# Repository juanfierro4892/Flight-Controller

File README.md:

Flight Controller 

This is a custom flight controller designed for control rockets.
It uses an STM32F722 microcontroller, ICM-45686 IMU, BMP580 barometer, and has a microSD card for logging flight data. It supports 2S LiPo batteries with onboard charging and has PWM outputs for controlling servos.

The board was designed in KiCad and is fully open source.

PCB: 

3D image: 

Schematic: 

Assembly:

There is no assembly instructions because as it have a lot of components there come assembled from the manufacturer aka JLCPCB

Technical Specifications
Brain: STM32F722RET6 microcontroller.

IMU: ICM-45686 high-precision motion sensor.

Barometer: BMP580 altitude tracker.

Actuation: Multi-channel Servo output via PWM.

Data Logging: Onboard MicroSD card slot.

Power Management:

BQ25883: 2-cell LiPo battery charger via USB-C.

TPS63070: 5V Buck-Boost regulator for servos.

LMR51430: 3.3V Buck regulator for the MCU and sensors..

D2: RGB LED (Common Anode) — Visual status indicator for system boot, ready-to-fly state, and critical errors (IMU, battery, SD card, and power rails).

It is coded in C in visual studio code.

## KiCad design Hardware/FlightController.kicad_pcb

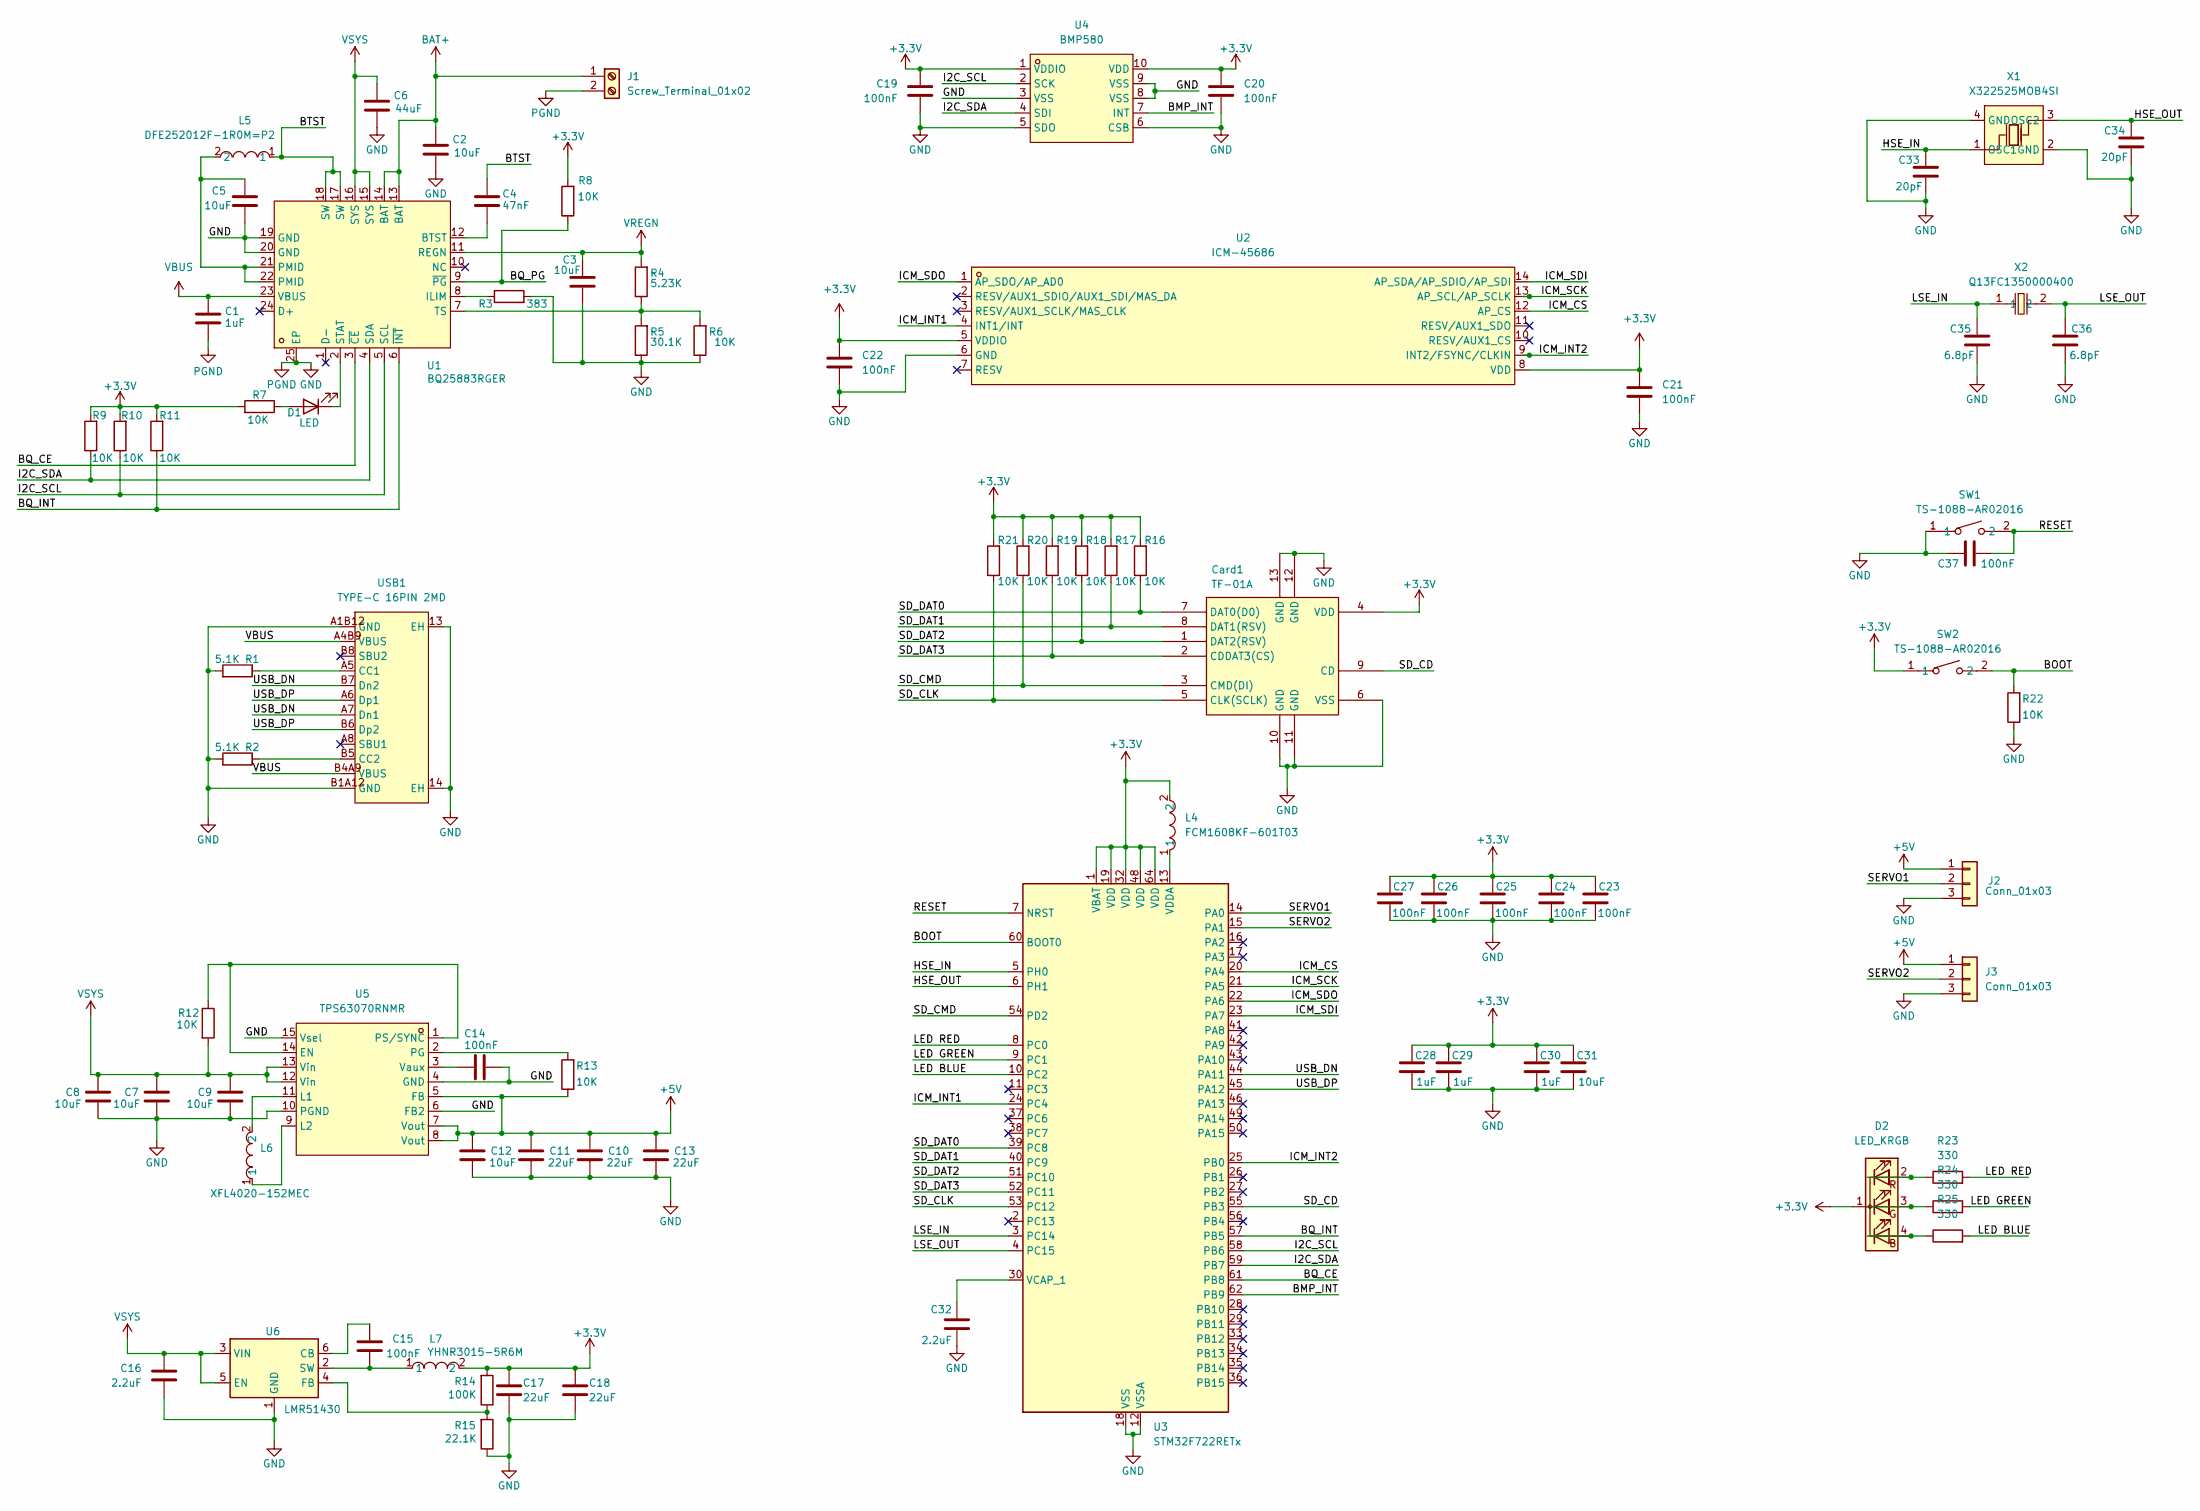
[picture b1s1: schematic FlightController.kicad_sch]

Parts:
C1, C28, C29, C30: 1uF; C_0402_1005Metric
C2, C9, C12: 10uF; C_0603_1608Metric
C3, C5, C31: 10uF; C_0402_1005Metric
C4: 47nF; C_0201_0603Metric
C6: 44uF; C_0603_1608Metric
C7, C8: 10uF; C_0805_2012Metric
C10, C11, C13: 22uF; C_0805_2012Metric
C14, C15, C19, C20, C21, C22, C23, C24, C25, C26, C27, C37: 100nF; C_0201_0603Metric
C16: 2.2uF; C_0603_1608Metric
C17, C18: 22uF; C_0402_1005Metric
C32: 2.2uF; C_0201_0603Metric
C33, C34: 20pF; C_0201_0603Metric
C35, C36: 6.8pF; C_0201_0603Metric
Card1: TF-01A; TF-SMD_TF-01A; LCSC Part C91145
D1: LED; LED_0402_1005Metric
D2: LED_KRGB; LED_Avago_PLCC4_3.2x2.8mm_CW
J1: Screw_Terminal_01x02; TerminalBlock_Xinya_XY308-2.54-2P_1x02_P2.54mm_Horizontal
J2, J3: Conn_01x03; PinHeader_1x03_P2.54mm_Vertical
L4: FCM1608KF-601T03; L0603; LCSC Part C141723
L5: DFE252012F-1R0M=P2; L2520; LCSC Part C435392
L6: XFL4020-152MEC; IND-SMD_L4.0-W4.0-A; LCSC Part C3033018
L7: YHNR3015-5R6M; IND-SMD_L3.0-W3.0; LCSC Part C18236327
R1, R2: 5.1K; R_0201_0603Metric
R3: 383; R_0201_0603Metric
R4: 5.23K; R_0201_0603Metric
R5: 30.1K; R_0201_0603Metric
R6, R7, R8, R9, R10, R11, R12, R13, R16, R17, R18, R19, R20, R21, R22: 10K; R_0201_0603Metric
R14: 100K; R_0402_1005Metric
R15: 22.1K; R_0402_1005Metric
R23, R24, R25: 330; R_0201_0603Metric
SW1, SW2: TS-1088-AR02016; SW-SMD_L3.9-W3.0-P4.45; LCSC Part C720477
U1: BQ25883RGER; VFQFPN-24_L4.0-W4.0-P0.50-BL-EP2.8; LCSC Part C544362
U2: ICM-45686; LGA-14_L3.0-W2.5-P0.50-TL; LCSC Part C22459454
U3: STM32F722RETx; LQFP-64_10x10mm_P0.5mm
U4: BMP580; LGA-10_L2.0-W2.0-P0.50-TL_BMP580; LCSC Part C22391138
U5: TPS63070RNMR; VQFN-HR-15_L3.0-W2.5-P0.50-BL_TPS63070RNMR; LCSC Part C109322
U6: LMR51430; SOT-23-6
USB1: TYPE-C 16PIN 2MD; USB-C-SMD_TYPE-C-16PIN-2MD-073; MPN TYPE-C 16PIN 2MD(073); LCSC Part C2765186
X1: X322525MOB4SI; CRYSTAL-SMD_4P-L3.2-W2.5-BL; LCSC Part C9006
X2: Q13FC1350000400; FC-135R_L3.2-W1.5; LCSC Part C32346

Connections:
+3.3V: C17.1, C18.1, C19.1, C20.1, C21.1, C22.1, C23.1, C24.1, C25.1, C26.1, C27.1, C28.1, C29.1, C30.1, C31.1, Card1.4 (VDD), D2.1 (K), L4.2, L7.2, R7.2, R8.2, R9.2, R10.2, R11.2, R14.2, R16.2, R17.2, R18.2, R19.2, R20.2, R21.2, SW2.1, U2.5 (VDDIO), U2.8 (VDD), U3.1 (VBAT), U3.19 (VDD), U3.32 (VDD), U3.48 (VDD), U3.64 (VDD), U4.1 (VDDIO), U4.10 (VDD)
+5V: C10.1, C11.1, C12.1, C13.1, J2.1, J3.1, R13.1, U5.5 (FB), U5.7 (Vout), U5.8 (Vout)
/BMP_INT: U3.62 (PB9), U4.7 (INT)
/BOOT: R22.2, SW2.2, U3.60 (BOOT0)
/BQ_CE: U1.3 (~CE), U3.61 (PB8)
/BQ_INT: R11.1, U1.6 (~INT), U3.57 (PB5)
/BQ_PG: R8.1, U1.9 (~PG)
/BTST: C4.1, L5.1, U1.17 (SW), U1.18 (SW)
/HSE_IN: C33.1, U3.5 (PH0), X1.1 (OSC1)
/HSE_OUT: C34.1, U3.6 (PH1), X1.3 (OSC2)
/I2C_SCL: R10.1, U1.5 (SCL), U3.58 (PB6), U4.2 (SCK)
/I2C_SDA: R9.1, U1.4 (SDA), U3.59 (PB7), U4.4 (SDI)
/ICM_CS: U2.12 (AP_CS), U3.20 (PA4)
/ICM_INT1: U2.4 (INT1/INT), U3.24 (PC4)
/ICM_INT2: U2.9 (INT2/FSYNC/CLKIN), U3.25 (PB0)
/ICM_SCK: U2.13 (AP_SCL/AP_SCLK), U3.21 (PA5)
/ICM_SDI: U2.14 (AP_SDA/AP_SDIO/AP_SDI), U3.23 (PA7)
/ICM_SDO: U2.1 (AP_SDO/AP_AD0), U3.22 (PA6)
/LED BLUE: R25.2, U3.10 (PC2)
/LED GREEN: R24.2, U3.9 (PC1)
/LED RED: R23.2, U3.8 (PC0)
/LSE_IN: C35.1, U3.3 (PC14), X2.1
/LSE_OUT: C36.1, U3.4 (PC15), X2.2
/RESET: C37.2, SW1.2, U3.7 (NRST)
/SD_CD: Card1.9 (CD), U3.55 (PB3)
/SD_CLK: Card1.5 (CLK(SCLK)), R21.1, U3.53 (PC12)
/SD_CMD: Card1.3 (CMD(DI)), R20.1, U3.54 (PD2)
/SD_DAT0: Card1.7 (DAT0(D0)), R16.1, U3.39 (PC8)
/SD_DAT1: Card1.8 (DAT1(RSV)), R17.1, U3.40 (PC9)
/SD_DAT2: Card1.1 (DAT2(RSV)), R18.1, U3.51 (PC10)
/SD_DAT3: Card1.2 (CDDAT3(CS)), R19.1, U3.52 (PC11)
/SERVO1: J2.2, U3.14 (PA0)
/SERVO2: J3.2, U3.15 (PA1)
/USB_DN: U3.44 (PA11), USB1.A7 (Dn1), USB1.B7 (Dn2)
/USB_DP: U3.45 (PA12), USB1.A6 (Dp1), USB1.B6 (Dp2)
BAT+: C2.1, J1.1, U1.13 (BAT), U1.14 (BAT)
GND: C1.2, C2.2, C3.2, C5.2, C6.2, C7.2, C8.2, C9.2, C10.2, C11.2, C12.2, C13.2, C14.2, C16.2, C17.2, C18.2, C19.2, C20.2, C21.2, C22.2, C23.2, C24.2, C25.2, C26.2, C27.2, C28.2, C29.2, C30.2, C31.2, C32.2, C33.2, C34.2, C35.2, C36.2, C37.1, Card1.6 (VSS), Card1.10 (GND), Card1.11 (GND), Card1.12 (GND), Card1.13 (GND), J1.2, J2.3, J3.3, R1.2, R2.2, R3.2, R5.1, R6.1, R15.1, R22.1, SW1.1, U1.19 (GND), U1.20 (GND), U1.25 (EP), U2.6 (GND), U3.12 (VSSA), U3.18 (VSS), U3.31 (VSS), U3.47 (VSS), U3.63 (VSS), U4.3 (VSS), U4.5 (SDO), U4.6 (CSB), U4.8 (VSS), U4.9 (VSS), U5.4 (GND), U5.6 (FB2), U5.10 (PGND), U5.15 (Vsel), U6.1 (GND), USB1.13 (EH), USB1.14 (EH), USB1.A1B12 (GND), USB1.B1A12 (GND), X1.2 (GND), X1.4 (GND)
unnamed: C5.1, L5.2, U1.21 (PMID), U1.22 (PMID)
unnamed: D1.2 (A), R7.1
unnamed: D1.1 (K), U1.2 (STAT)
unnamed: D2.4 (BA), R25.1
unnamed: D2.3 (GA), R24.1
unnamed: D2.2 (RA), R23.1
unnamed: C4.2, U1.12 (BTST)
unnamed: R3.1, U1.8 (ILIM)
unnamed: R4.1, R5.2, R6.2, U1.7 (TS)
unnamed: C32.1, U3.30 (VCAP_1)
unnamed: L4.1, U3.13 (VDDA)
unnamed: R12.1, U5.1 (PS/SYNC), U5.14 (EN)
unnamed: L6.2, U5.11 (L1)
unnamed: L6.1, U5.9 (L2)
unnamed: R13.2, U5.2 (PG)
unnamed: C14.1, U5.3 (Vaux)
unnamed: C15.1, U6.6 (CB)
unnamed: R14.1, R15.2, U6.4 (FB)
unnamed: C15.2, L7.1, U6.2 (SW)
unnamed: R1.1, USB1.A5 (CC1)
unnamed: R2.1, USB1.B5 (CC2)
VBUS: C1.1, U1.23 (VBUS), USB1.A4B9 (VBUS), USB1.B4A9 (VBUS)
VREGN: C3.1, R4.2, U1.11 (REGN)
VSYS: C6.1, C7.1, C8.1, C9.1, C16.1, R12.2, U1.15 (SYS), U1.16 (SYS), U5.12 (Vin), U5.13 (Vin), U6.3 (VIN), U6.5 (EN)

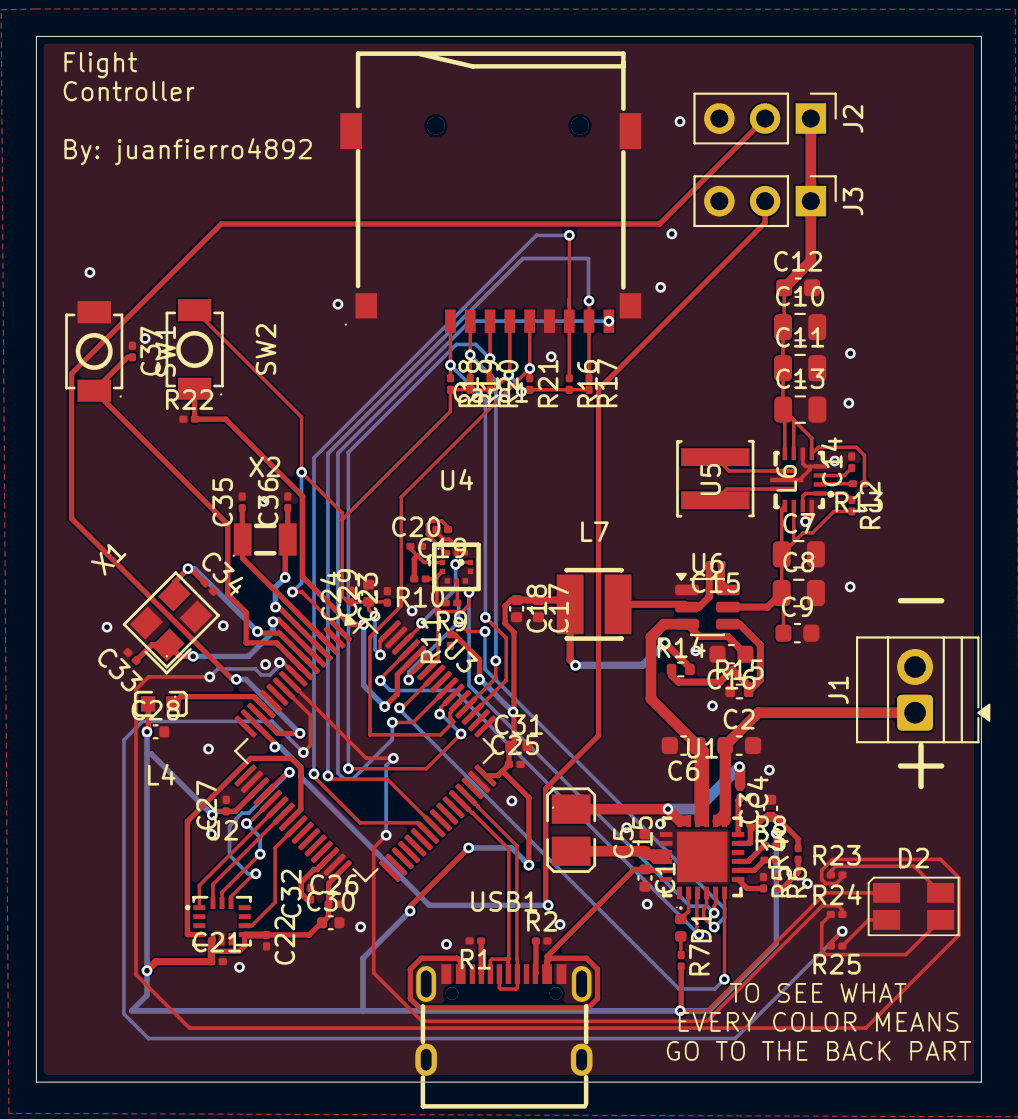
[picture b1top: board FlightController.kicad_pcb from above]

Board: 2 copper layers, 52.5 x 58.1 mm, 83 parts (0 on the bottom side), 61 nets.

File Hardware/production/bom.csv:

Designator,Footprint,Quantity,Value,LCSC Part #
"C1, C28, C29, C30",0402,4,1uF,
"C10, C11, C13",0805,3,22uF,
"C12, C2, C9",0603,3,10uF,
"C14, C15, C19, C20, C21, C22, C23, C24, C25, C26, C27, C37",0201,12,100nF,
C16,0603,1,2.2uF,
"C17, C18",0402,2,22uF,
"C3, C31, C5",0402,3,10uF,
C32,0201,1,2.2uF,
"C33, C34",0201,2,20pF,
"C35, C36",0201,2,6.8pF,
C4,0201,1,47nF,
C6,0603,1,44uF,
"C7, C8",0805,2,10uF,
CARD1,TF-SMD_TF-01A,1,TF-01A,C91145
D1,0402,1,LED,
D2,LED_Avago_PLCC4_3.2x2.8mm_CW,1,LED_KRGB,
J1,TerminalBlock_Xinya_XY308-2.54-2P_1x02_P2.54mm_Horizontal,1,Screw_Terminal_01x02,
"J2, J3",PinHeader_1x03_P2.54mm_Vertical,2,Conn_01x03,
L4,L0603,1,FCM1608KF-601T03,C141723
L5,L2520,1,DFE252012F-1R0M=P2,C435392
L6,IND-SMD_L4.0-W4.0-A,1,XFL4020-152MEC,C3033018
L7,IND-SMD_L3.0-W3.0,1,YHNR3015-5R6M,C18236327
"R1, R2",0201,2,5.1K,
"R10, R11, R12, R13, R16, R17, R18, R19, R20, R21, R22, R6, R7, R8, R9",0201,15,10K,
R14,0402,1,100K,
R15,0402,1,22.1K,
"R23, R24, R25",0201,3,330,
R3,0201,1,383,
R4,0201,1,5.23K,
R5,0201,1,30.1K,
"SW1, SW2",SW-SMD_L3.9-W3.0-P4.45,2,TS-1088-AR02016,C720477
U1,VFQFPN-24_L4.0-W4.0-P0.50-BL-EP2.8,1,BQ25883RGER,C544362
U2,LGA-14_L3.0-W2.5-P0.50-TL,1,ICM-45686,C22459454
U3,LQFP-64_10x10mm_P0.5mm,1,STM32F722RETx,
U4,LGA-10_L2.0-W2.0-P0.50-TL_BMP580,1,BMP580,C22391138
U5,VQFN-HR-15_L3.0-W2.5-P0.50-BL_TPS63070RNMR,1,TPS63070RNMR,C109322
U6,SOT-23-6,1,LMR51430,
USB1,USB-C-SMD_TYPE-C-16PIN-2MD-073,1,TYPE-C 16PIN 2MD,C2765186
X1,CRYSTAL-SMD_4P-L3.2-W2.5-BL,1,X322525MOB4SI,C9006
X2,FC-135R_L3.2-W1.5,1,Q13FC1350000400,C32346

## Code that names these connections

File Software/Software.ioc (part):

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Mcu.Name=STM32F722R(C-E)Tx
Mcu.Package=LQFP64
Mcu.UserName=STM32F722RETx
PA0-WKUP.Signal=S_TIM2_CH1_ETR
PA1.Signal=S_TIM2_CH2
PA11.Mode=Host_Only
PA11.Signal=USB_OTG_FS_DM
PA12.Mode=Host_Only
PA12.Signal=USB_OTG_FS_DP
PA4.Mode=NSS_Signal_Hard_Output
PA4.Signal=SPI1_NSS
PA5.Mode=Full_Duplex_Master
PA5.Signal=SPI1_SCK
PA6.Mode=Full_Duplex_Master
PA6.Signal=SPI1_MISO
PA7.Mode=Full_Duplex_Master
PA7.Signal=SPI1_MOSI
PB3.GPIOParameters=GPIO_Label
PB3.GPIO_Label=SD_CS
PB3.Signal=GPIO_Input
PB5.GPIOParameters=GPIO_Label
PB5.GPIO_Label=BQ_INT
PB5.Signal=GPXTI5
PB6.Mode=I2C
PB6.Signal=I2C1_SCL
PB7.Mode=I2C
PB7.Signal=I2C1_SDA
PB8.GPIOParameters=GPIO_Label
PB8.GPIO_Label=BQ_CE
PB8.Signal=GPIO_Output
PB9.GPIOParameters=GPIO_Label
PB9.GPIO_Label=BMP_INT
PB9.Signal=GPXTI9
PC0.GPIOParameters=GPIO_Label
PC0.GPIO_Label=LED R
PC0.Signal=GPIO_Output
PC1.GPIOParameters=GPIO_Label
PC1.GPIO_Label=LED G
PC1.Signal=GPIO_Output
PC10.Mode=SD_4_bits_Wide_bus
PC10.Signal=SDMMC1_D2
PC11.Mode=SD_4_bits_Wide_bus
PC11.Signal=SDMMC1_D3
PC12.Mode=SD_4_bits_Wide_bus
PC12.Signal=SDMMC1_CK
PC14-OSC32_IN.Mode=LSE-External-Oscillator
PC14-OSC32_IN.Signal=RCC_OSC32_IN
PC15-OSC32_OUT.Mode=LSE-External-Oscillator
PC15-OSC32_OUT.Signal=RCC_OSC32_OUT
PC2.GPIOParameters=GPIO_Label
PC2.GPIO_Label=LED B
PC2.Signal=GPIO_Output
PC4.GPIOParameters=GPIO_Label
PC4.GPIO_Label=ICM_INT1
PC4.Signal=GPXTI4
PC8.Mode=SD_4_bits_Wide_bus
PC8.Signal=SDMMC1_D0
PC9.Mode=SD_4_bits_Wide_bus
PC9.Signal=SDMMC1_D1
PD2.Mode=SD_4_bits_Wide_bus
PD2.Signal=SDMMC1_CMD
PH0-OSC_IN.Mode=HSE-External-Oscillator
PH0-OSC_IN.Signal=RCC_OSC_IN
PH1-OSC_OUT.Mode=HSE-External-Oscillator
PH1-OSC_OUT.Signal=RCC_OSC_OUT
RCC.HSE_VALUE=25000000
board=custom

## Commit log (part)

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2026-05-25 Uploading all the files of the software, hardware and production to the REPO
2026-05-25 Add README for flight controller project
    Added detailed specifications and description for the flight controller project.
